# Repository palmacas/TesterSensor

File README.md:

# TesterSensor

This board can be used to test 3-wire industrial sensors without connecting it to a PLC. The voltage input reads values between 0 and 10V and the current input reads values between 0 and 20mA.  
Requires a 12V DC power source.

---
More information:  
[Tester para sensores industriales [Spanish]](https://palmacas.com/tester-para-sensores-industriales/)

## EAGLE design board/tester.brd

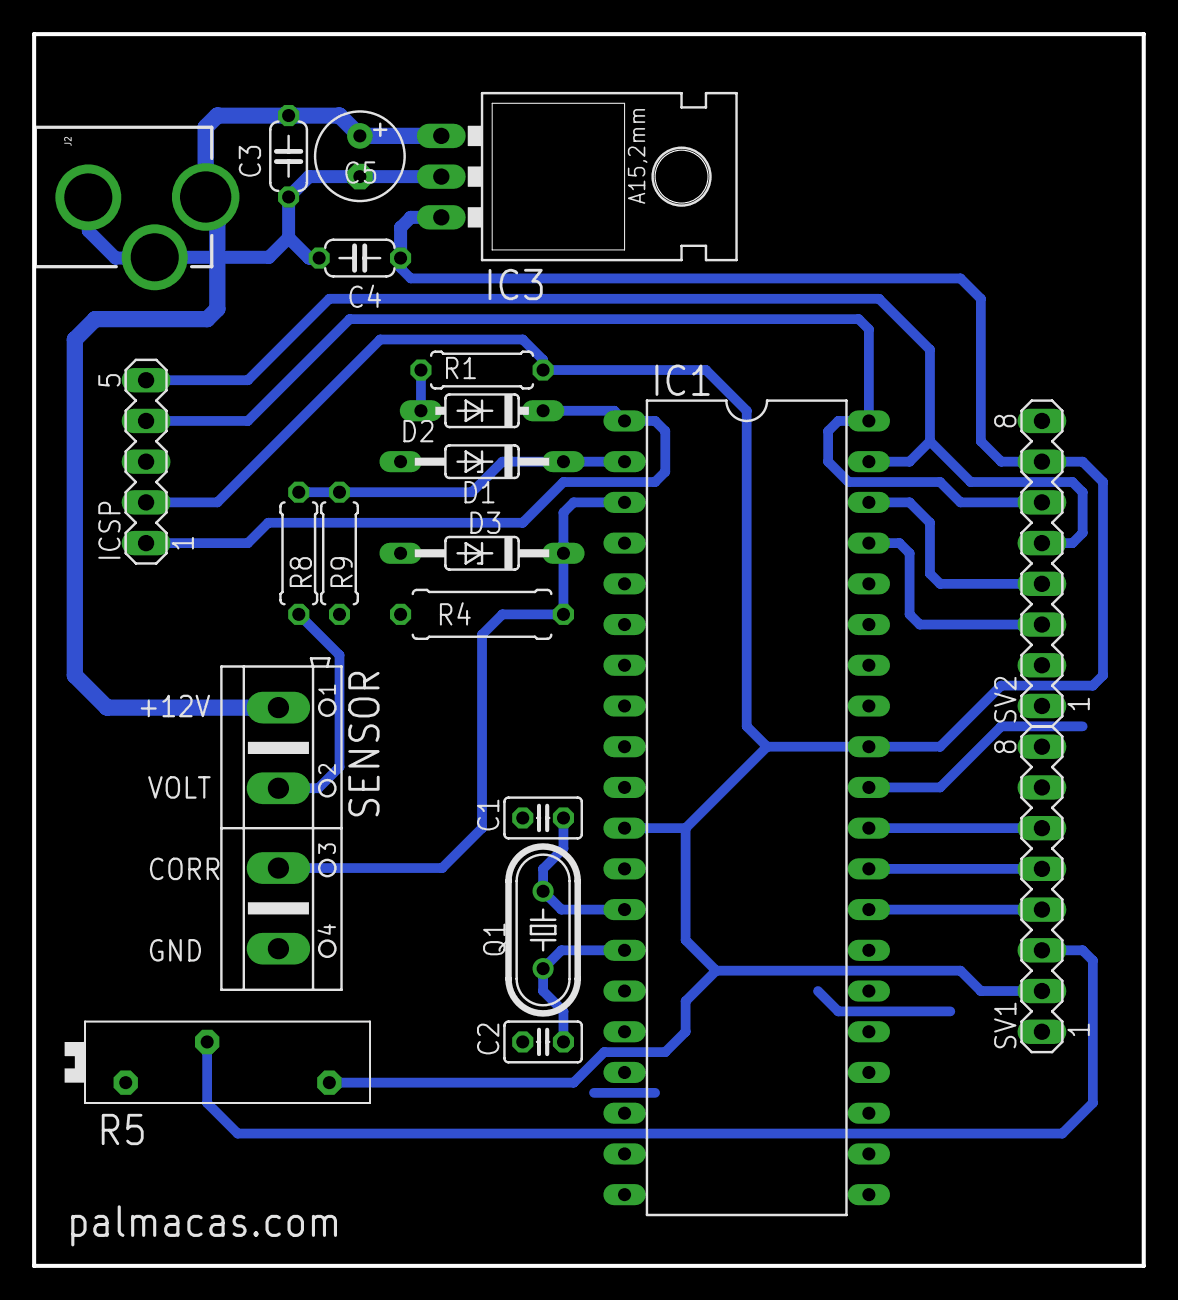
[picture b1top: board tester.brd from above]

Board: 2 copper layers, 69.2 x 76.8 mm, 21 parts (0 on the bottom side), 18 nets.

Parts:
C1, C2: 22pF; C025-025X050
C3, C4: 100nF; C050-024X044
C5: 47uF; E2,5-6
D1, D3: 5.1V; DO35Z10
D2: 1N4148DO35-7; DO35-7
IC1: PIC16F877P; DIL40
IC3: 7805; 78XXL
ICSP: SV1; MA05-1
J2: POWER_JACKPTH_LOCK; POWER_JACK_PTH_LOCK
Q1: 6MHz; HC49/S
R1, R8, R9: 10K; 0207/7
R4: 220; 0309/10
R5: 1K; PT-SPIN
SENSOR: X1; AK500/4
SV1, SV2: MA08-1

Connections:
+5V: C4.1, IC1.11, IC1.32, IC3.OUT, ICSP.2, R1.2, R5.2, SV1.2, SV2.7
+12V: C3.1, C5.+, IC3.IN, J2.PWR, SENSOR.1
GND: C1.2, C2.2, C3.2, C4.2, C5.-, D1.A, D3.A, IC1.12, IC1.31, IC3.GND, ICSP.3, J2.GND, J2.GNDBREAK, R4.1, R5.1, R9.2, SENSOR.4, SV1.1, SV2.8
IN_COR: D3.C, IC1.3, R4.2, SENSOR.3
IN_VOL: R8.2, SENSOR.2
unnamed: R5.3, SV1.3
unnamed: D2.A, R1.1
unnamed: IC1.38, SV2.4
unnamed: IC1.37, SV2.3
unnamed: IC1.30, SV1.6
unnamed: IC1.29, SV1.5
unnamed: IC1.28, SV1.4
unnamed: D1.C, IC1.2, R8.1, R9.1
OSC1: C1.1, IC1.13, Q1.1
OSC2: C2.1, IC1.14, Q1.2
PGC: IC1.39, ICSP.5, SV2.5
PGD: IC1.40, ICSP.4, SV2.6
VPP: D2.C, IC1.1, ICSP.1

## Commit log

2020-06-02 Code update
2020-06-03 Update LICENSE
2022-08-21 Rename code/tester_sensor.hex to Firmware/tester_sensor.hex
2022-08-21 Rename code/flex_lcd.c to Firmware/flex_lcd.c
2022-08-21 Rename code/tester_sensor.c to Firmware/tester_sensor.c
2022-08-21 Rename Firmware/tester_sensor.hex to firmware/tester_sensor.hex
2022-08-21 Rename Firmware/flex_lcd.c to firmware/flex_lcd.c
2022-08-21 Rename Firmware/tester_sensor.c to firmware/tester_sensor.c
